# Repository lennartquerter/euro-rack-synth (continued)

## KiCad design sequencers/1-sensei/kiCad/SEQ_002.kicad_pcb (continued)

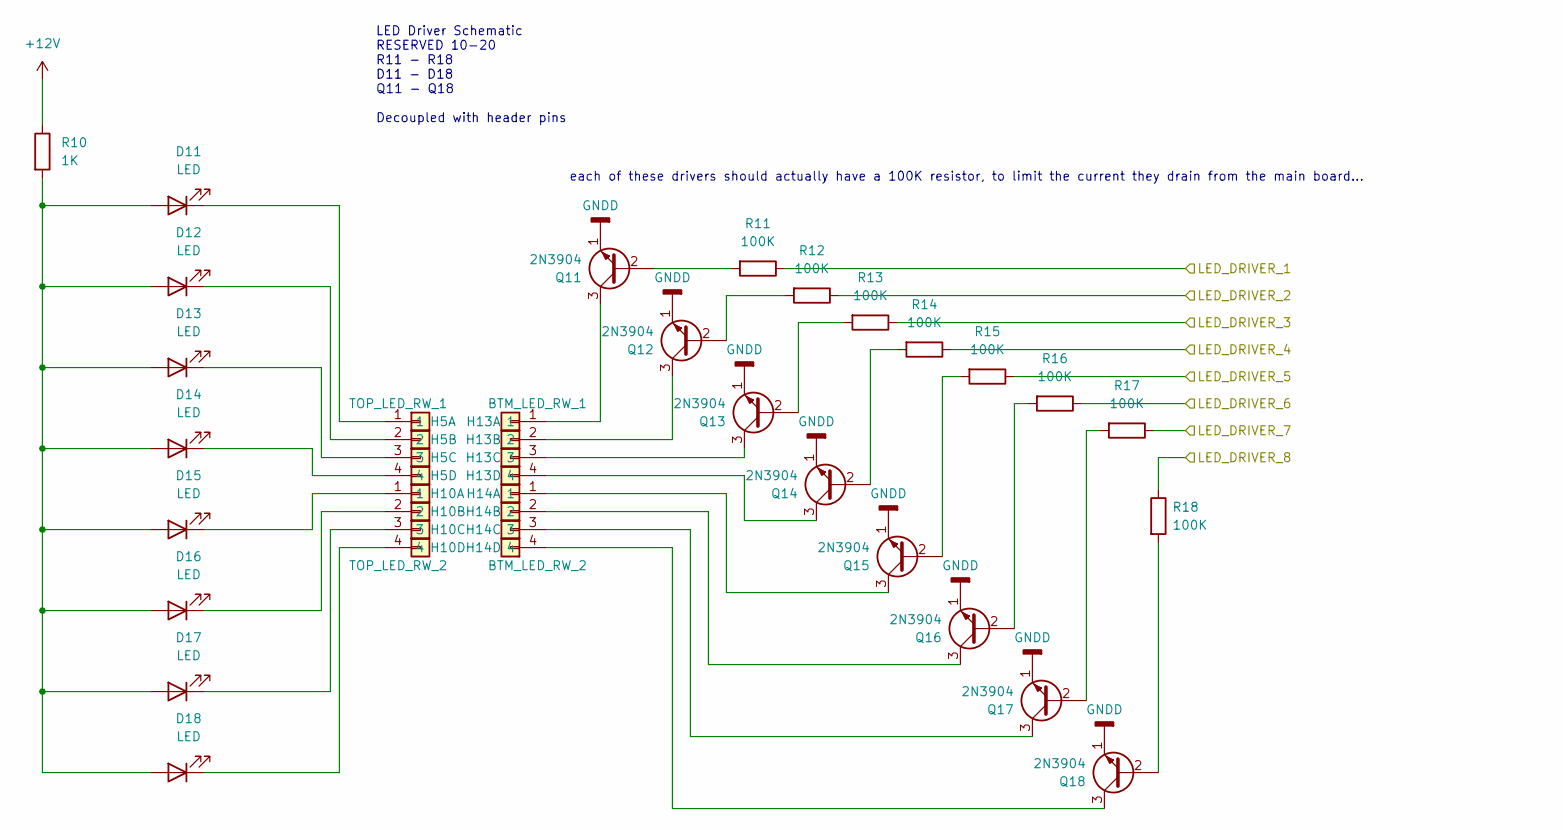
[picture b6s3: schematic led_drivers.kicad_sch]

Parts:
D11, D12, D13, D14, D15, D16, D17, D18: LED; LED_D3.0mm
H5: TOP_LED_RW_1; PinHeader_1x04_P2.00mm_Vertical
H10: TOP_LED_RW_2; PinHeader_1x04_P2.00mm_Vertical
H13: BTM_LED_RW_1; PinSocket_1x04_P2.00mm_Vertical
H14: BTM_LED_RW_2; PinSocket_1x04_P2.00mm_Vertical
Q11, Q12, Q13, Q14, Q15, Q16, Q17, Q18: 2N3904; TO-92_Inline
R10: 1K; R_Axial_DIN0207_L6.3mm_D2.5mm_P10.16mm_Horizontal
R11, R12, R13, R14, R15, R16, R17, R18: 100K; R_Axial_DIN0207_L6.3mm_D2.5mm_P10.16mm_Horizontal

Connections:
+12V: R10.1; also elsewhere on the board
/led_drivers/LED_DRIVER_1: Q11.2 (B), R11.2; also elsewhere on the board
/led_drivers/LED_DRIVER_2: Q12.2 (B), R12.2; also elsewhere on the board
/led_drivers/LED_DRIVER_3: Q13.2 (B), R13.2; also elsewhere on the board
/led_drivers/LED_DRIVER_4: Q14.2 (B), R14.2; also elsewhere on the board
/led_drivers/LED_DRIVER_5: Q15.2 (B), R15.2; also elsewhere on the board
/led_drivers/LED_DRIVER_6: Q16.2 (B), R16.2; also elsewhere on the board
/led_drivers/LED_DRIVER_7: Q17.2 (B), R17.2; also elsewhere on the board
/led_drivers/LED_DRIVER_8: Q18.2 (B), R18.2; also elsewhere on the board
GNDD: Q11.1 (E), Q12.1 (E), Q13.1 (E), Q14.1 (E), Q15.1 (E), Q16.1 (E), Q17.1 (E), Q18.1 (E); also elsewhere on the board
unnamed: D11.2 (A), D12.2 (A), D13.2 (A), D14.2 (A), D15.2 (A), D16.2 (A), D17.2 (A), D18.2 (A), R10.2
unnamed: D11.1 (K), H5.1
unnamed: D12.1 (K), H5.2
unnamed: D13.1 (K), H5.3
unnamed: D14.1 (K), H5.4
unnamed: D15.1 (K), H10.1
unnamed: D16.1 (K), H10.2
unnamed: D17.1 (K), H10.3
unnamed: D18.1 (K), H10.4
unnamed: H13.1, Q11.3 (C)
unnamed: H13.2, Q12.3 (C)
unnamed: H13.3, Q13.3 (C)
unnamed: H13.4, Q14.3 (C)
unnamed: H14.1, Q15.3 (C)
unnamed: H14.2, Q16.3 (C)
unnamed: H14.3, Q17.3 (C)
unnamed: H14.4, Q18.3 (C)

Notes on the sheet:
each of these drivers should actually have a 100K resistor, to limit the current they drain from the main board...
LED Driver Schematic RESERVED 10-20 R11 - R18 D11 - D18 Q11 - Q18 Decoupled with header pins

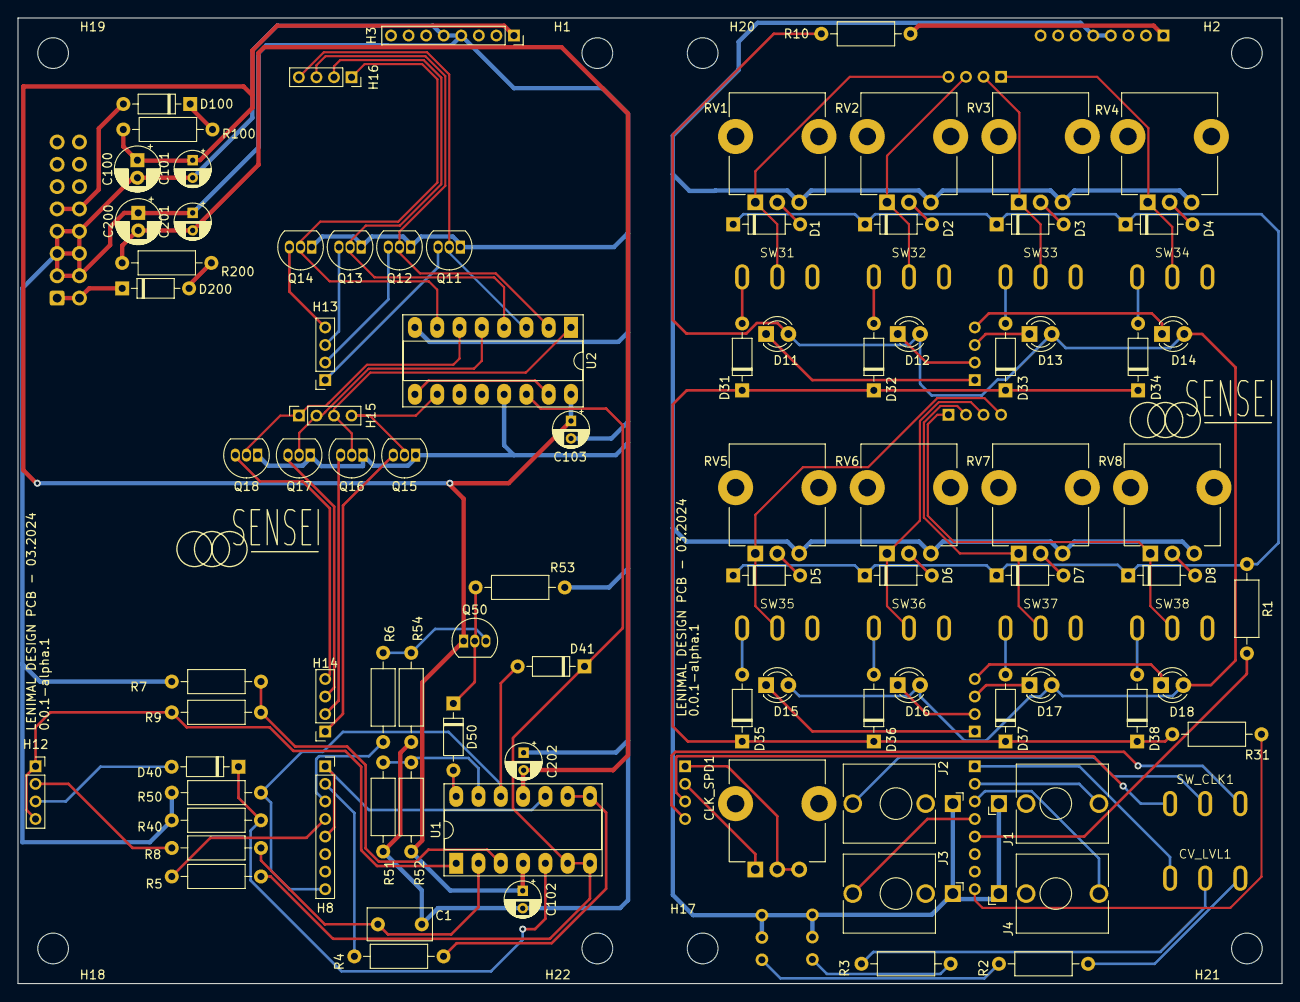
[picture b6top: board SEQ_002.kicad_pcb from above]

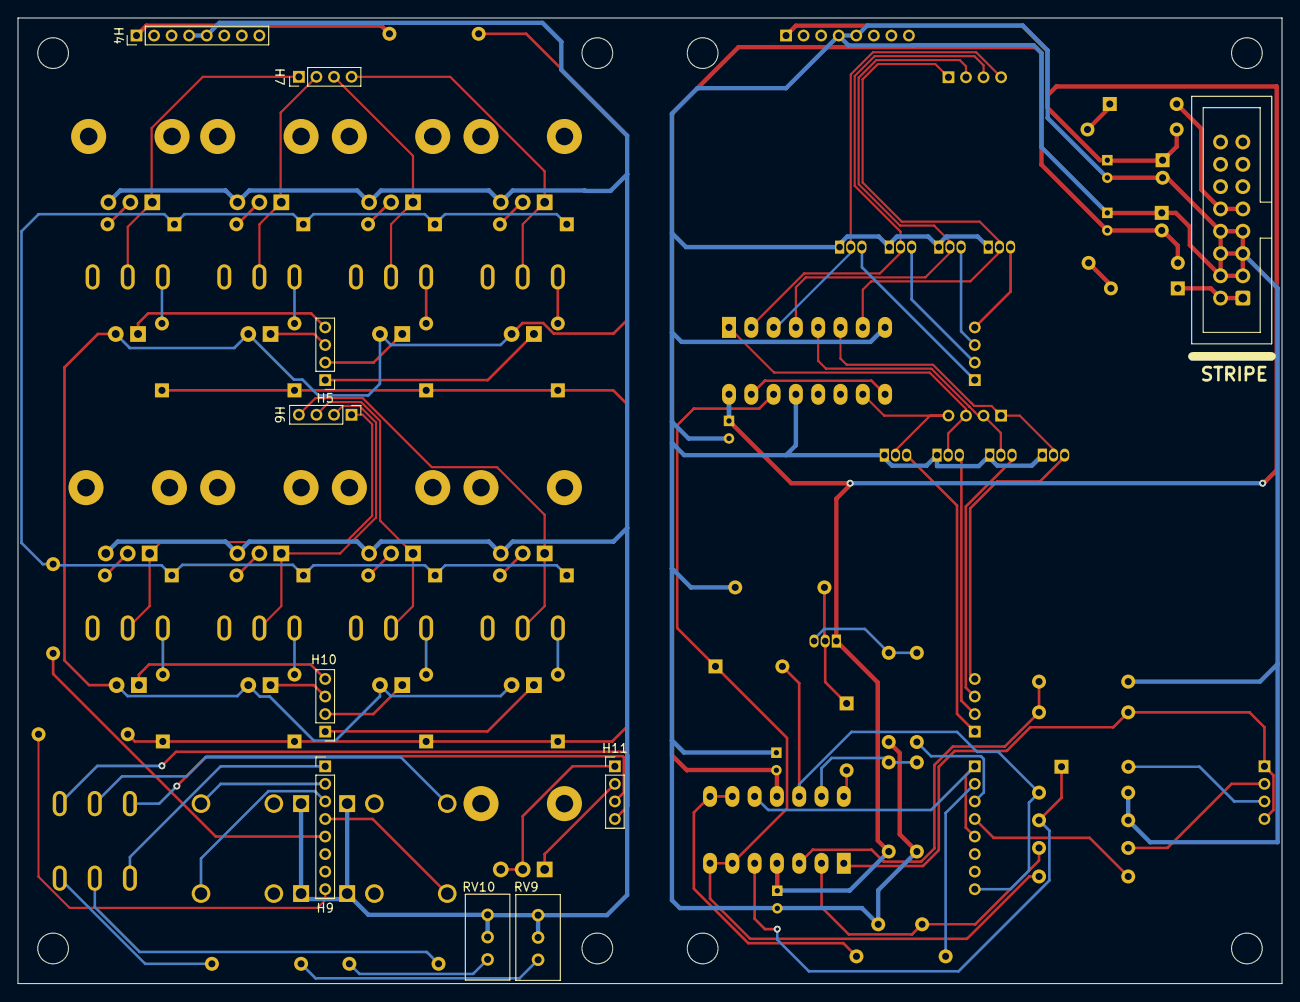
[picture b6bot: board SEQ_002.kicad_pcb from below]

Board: 2 copper layers, 144.0 x 110.0 mm, 115 parts (10 on the bottom side), 91 nets.
